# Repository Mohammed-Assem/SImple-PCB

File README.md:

# LED Pushbutton Circuit with KiCad

## 📘 Description
A simple KiCad project that includes a battery-powered LED circuit with three push buttons. Each button lights a separate LED when pressed.

## Bill of Materials (BOM)

| Component        | Quantity | Notes                        |
|------------------|----------|------------------------------|
| Resistor (R)     | 3        | 220Ω recommended             |
| LED              | 3        | Red/Green/Blue               |
| Push Button      | 3        | THT push button              |
| Battery Holder   | 1        | 9V or coin cell holder       |
| Battery          | 1        | 9V or CR2032                 |
| PCB              | 1        | Custom made using KiCad      |

## 🖼️ Screenshots

### Schematic  

### PCB Layout  

### 3D View  

## 💬 Slack Username
`@Mohamed Assem`

---

## 🛠️ Files Included
- KiCad project files (`.kicad_sch`, `.kicad_pcb`, etc.)
- Gerber files (in `/gerbers` folder)
- Drill files
- Screenshots

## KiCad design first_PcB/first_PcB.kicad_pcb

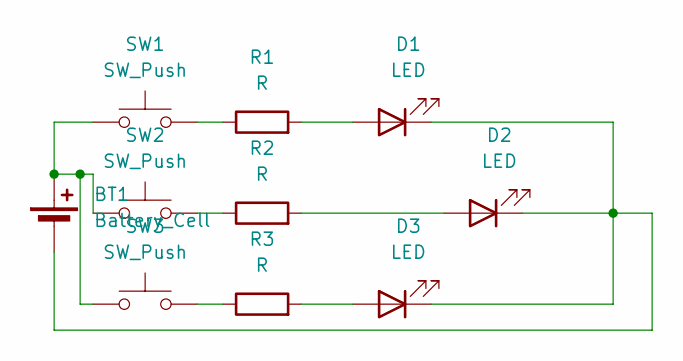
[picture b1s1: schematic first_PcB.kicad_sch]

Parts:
BT1: Battery_Cell; BatteryHolder_Keystone_3034_1x20mm
D1, D2, D3: LED; LED_D5.0mm
R1, R2, R3: R; R_Axial_DIN0207_L6.3mm_D2.5mm_P7.62mm_Horizontal
SW1, SW2, SW3: SW_Push; SW_PUSH_6mm

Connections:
unnamed: BT1.1 (+), SW1.1, SW2.1, SW3.1
unnamed: BT1.2 (-), D1.1 (K), D2.1 (K), D3.1 (K)
unnamed: D1.2 (A), R1.2
unnamed: D2.2 (A), R2.2
unnamed: D3.2 (A), R3.2
unnamed: R1.1, SW1.2
unnamed: R2.1, SW2.2
unnamed: R3.1, SW3.2

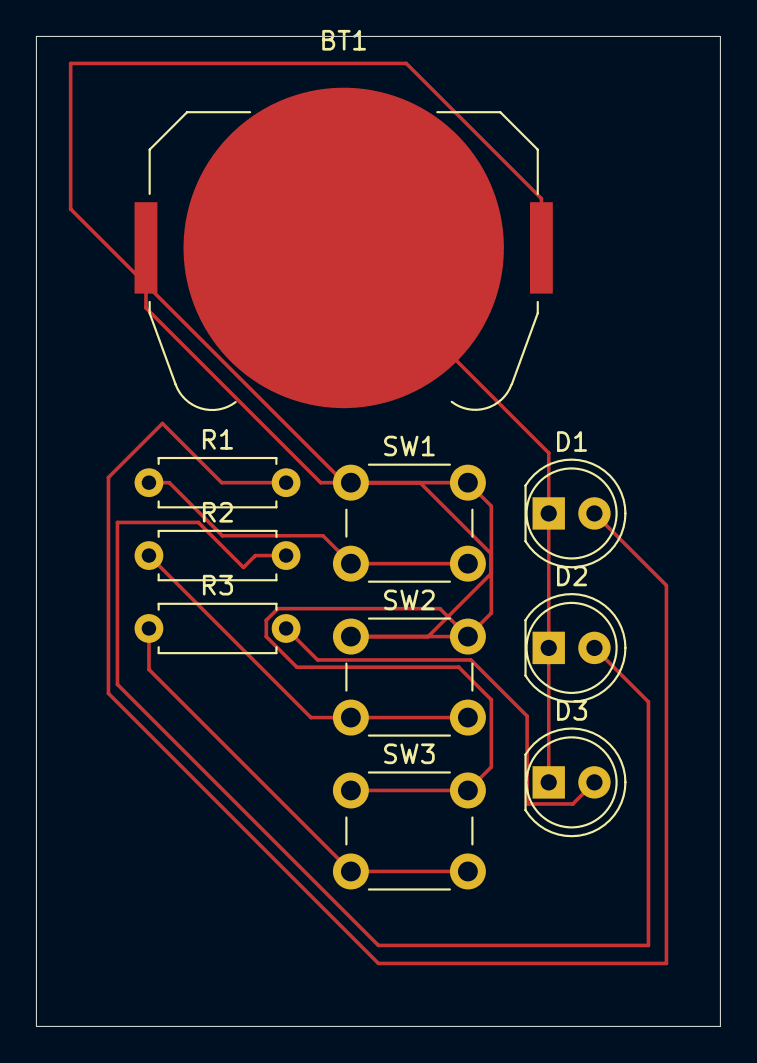
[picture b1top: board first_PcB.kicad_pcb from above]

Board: 2 copper layers, 38.0 x 55.0 mm, 10 parts (0 on the bottom side), 8 nets.
